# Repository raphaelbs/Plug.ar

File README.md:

# Plug.ar

Plug.ar é um projeto de conclusão de curso desenvolvido por Raphael Brandão para a Faculdade Pitágoras.

# Descrição

A ideia base do projeto é o desenvolvimento de uma caixa de tomada conectada e modular.

_Primeira versão do Plug.ar_

### Conectividade

A caixa será concetada à internet através do ESP8266 e também criará uma rede HTTP interna. Esta rede HTTP interna será usada por outros dispositivos Plug.ar da mesma residência para realizar comunicação entre-si mesmo sem acesso à internet.

_Plug.ar e o ESP8266_

### Modularização

A caixa de tomada será um container de módulos. O usuário final irá escolher qual módulo utilizar, quando necessário. Por exemplo, se o usuário deseja carregar o celular, poderá inserir um módulo de porta USB diretamente na sua tomada.

_Modularização do Plug.ar_

# Etapas

O projeto conta com 3 etapas:
* [x] 2/2016 [**Estágio 1**](./Estágio%201) estruturação física do projeto com CAD e impressão 3D
* [x] 1/2017 [**Estágio 2**](./Estágio%202) prototipagem eletrônica e interligação com o projeto físico
* [ ] 2/2017 **TCC** desenvolvimento do firmware, cliente web e mobile

# Sobre

Estudante de Engenharia de Controle e Automação - Faculdade Pitágoras.
Gerente de Projetos e Full Stack Developer - Find Soluções Coorporativas LTDA.
Divinópolis, Minas Gerais, Brasil.

_raphael.b.souza@hotmail.com_

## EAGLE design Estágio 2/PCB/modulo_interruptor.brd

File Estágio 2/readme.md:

# Estágio obrigatório 2

Esta etapa do projeto foi concluida em 06/2017.
Leia o [relatório final](./relatorio_final.pdf).

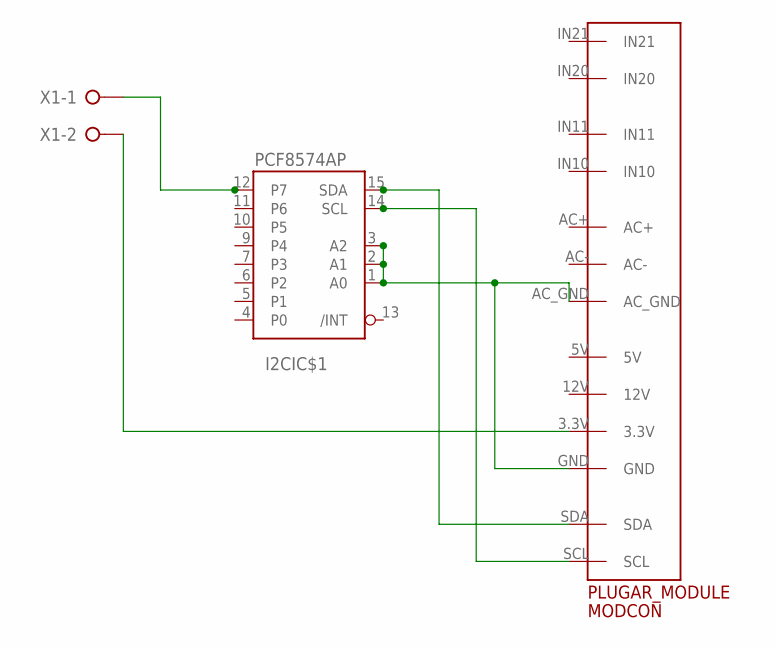
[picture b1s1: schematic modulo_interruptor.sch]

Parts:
I2C: PCF8574AP; DIL16
MODCON: PLUGARPADS; PLUGAR
X1: W237-02P; W237-132

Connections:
GND: I2C.1 (A0), I2C.2 (A1), I2C.3 (A2), I2C.8 (GND), MODCON.AC_GND, MODCON.GND
unnamed: MODCON.3.3V, X1.2
unnamed: I2C.12 (P7), X1.1
unnamed: I2C.14 (SCL), MODCON.SCL
unnamed: I2C.15 (SDA), MODCON.SDA
VCC: I2C.16 (VCC)

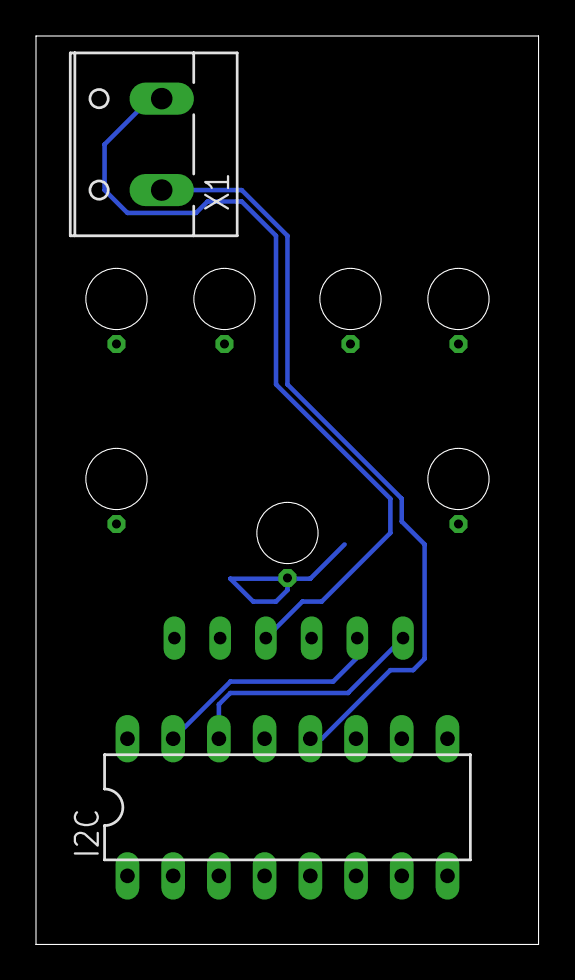
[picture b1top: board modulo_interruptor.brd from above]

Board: 2 copper layers, 27.9 x 50.5 mm, 3 parts (0 on the bottom side), 5 nets.

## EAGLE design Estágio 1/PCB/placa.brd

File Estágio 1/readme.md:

# Estágio obrigatório 1

Esta etapa do projeto foi concluida em 12/2016.
Leia o [relatório final](./relatorio_final.pdf).

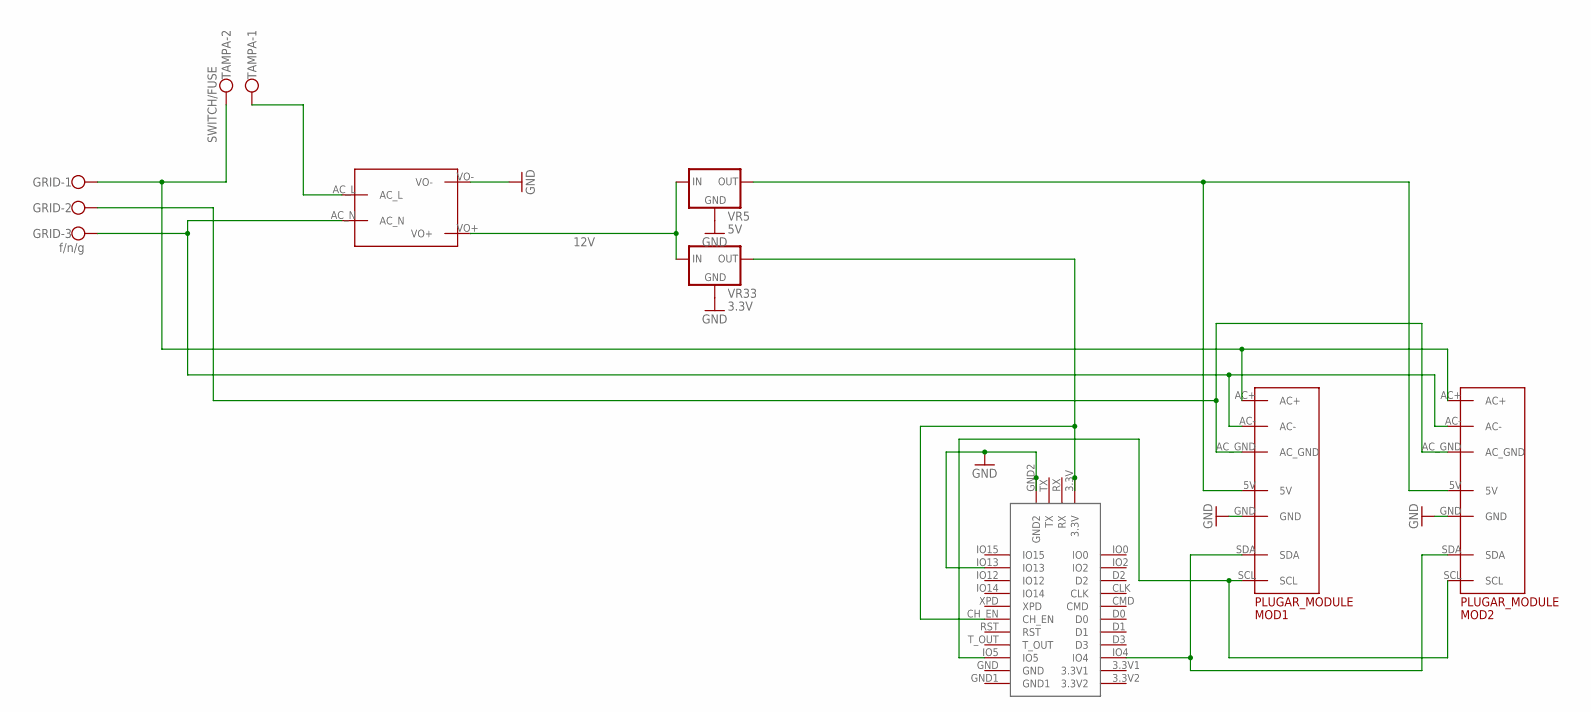
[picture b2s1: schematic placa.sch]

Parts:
GRID: f/n/g; W237-103
MOD1, MOD2: PLUGARPADS; PLUGAR
TAMPA: SWITCH/FUSE; W237-102
U$1: MAINS_CONVERTERS; HLK-PM01
U$2: ESP-201
VR5: 5V; 78LXX
VR33: 3.3V; 78LXX

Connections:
3.3V: U$2.3.3V, U$2.CH_EN, VR33.OUT
5V: MOD1.5V, MOD2.5V, VR5.OUT
12V: U$1.VO+, VR5.IN, VR33.IN
AC+: GRID.1, MOD1.AC+, MOD2.AC+, TAMPA.2
AC-: GRID.3, MOD1.AC-, MOD2.AC-, U$1.AC_N
AC_GND: GRID.2, MOD1.AC_GND, MOD2.AC_GND
GND: MOD1.GND, MOD2.GND, U$1.VO-, U$2.GND2, U$2.IO13, VR5.GND, VR33.GND
unnamed: TAMPA.1, U$1.AC_L
SCL: MOD1.SCL, MOD2.SCL, U$2.IO5
SDA: MOD1.SDA, MOD2.SDA, U$2.IO4

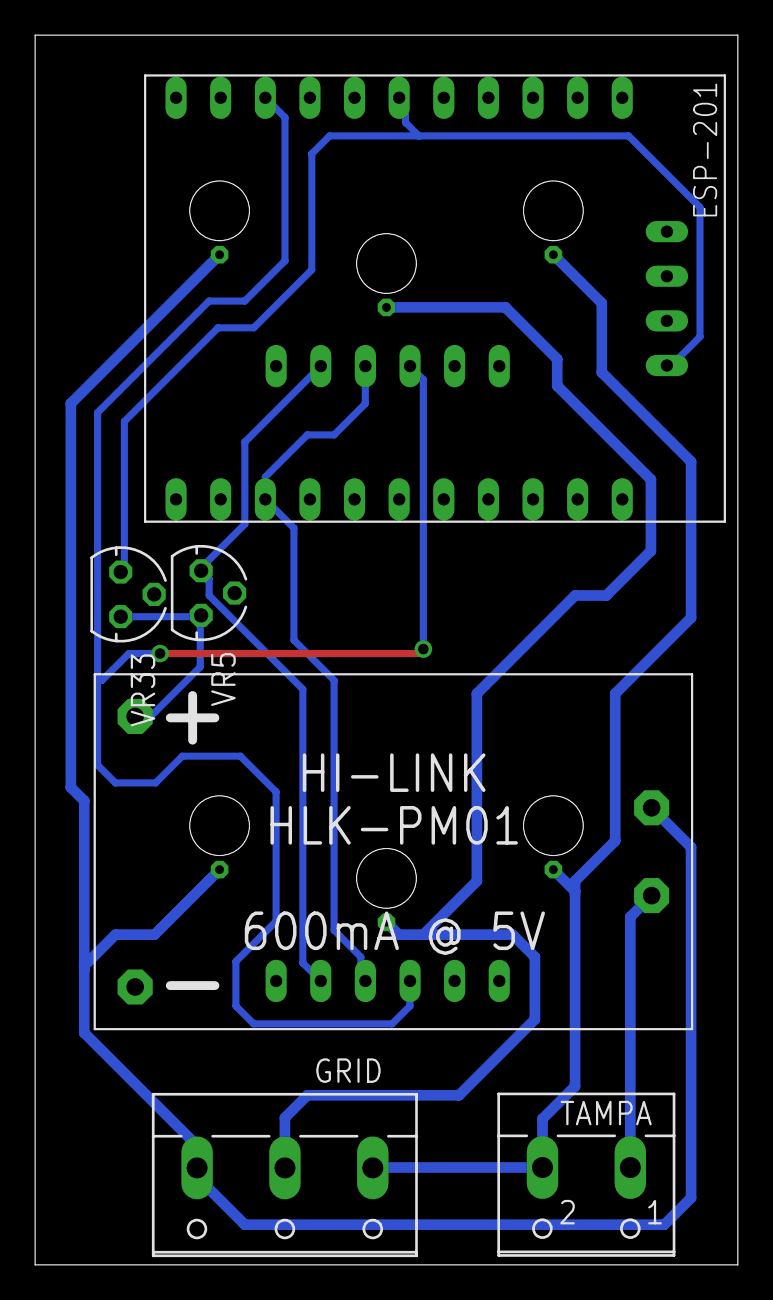
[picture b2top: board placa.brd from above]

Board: 2 copper layers, 40.0 x 70.0 mm, 8 parts (0 on the bottom side), 10 nets.

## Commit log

2017-04-16 commit inicial do projeto Plug.ar
2017-04-16 atualizando o read.me
2017-04-16 atualizando README.md com links
2017-04-16 inserindo infraestrutura do projeto web
2017-04-16 inserindo logistica de login
2017-04-16 terminado toolbar
2017-04-16 view home estruturada
2017-04-16 logando usuários
2017-04-16 inserindo comentarios e alterando o estado do led
2017-04-16 terminado webapp para lâmpada
2017-04-16 corrigido layoyt de mobile
2017-04-16 inserindo videofeed
2017-04-16 inserindo video feed
2017-04-16 adicionando usuario nodeMCU
2017-04-21 updating firebase, ESP and old files
2017-06-08 adicionado segunda etapa do projeto
2017-06-08 alterando docx para pdf
2017-06-08 Set theme jekyll-theme-architect
